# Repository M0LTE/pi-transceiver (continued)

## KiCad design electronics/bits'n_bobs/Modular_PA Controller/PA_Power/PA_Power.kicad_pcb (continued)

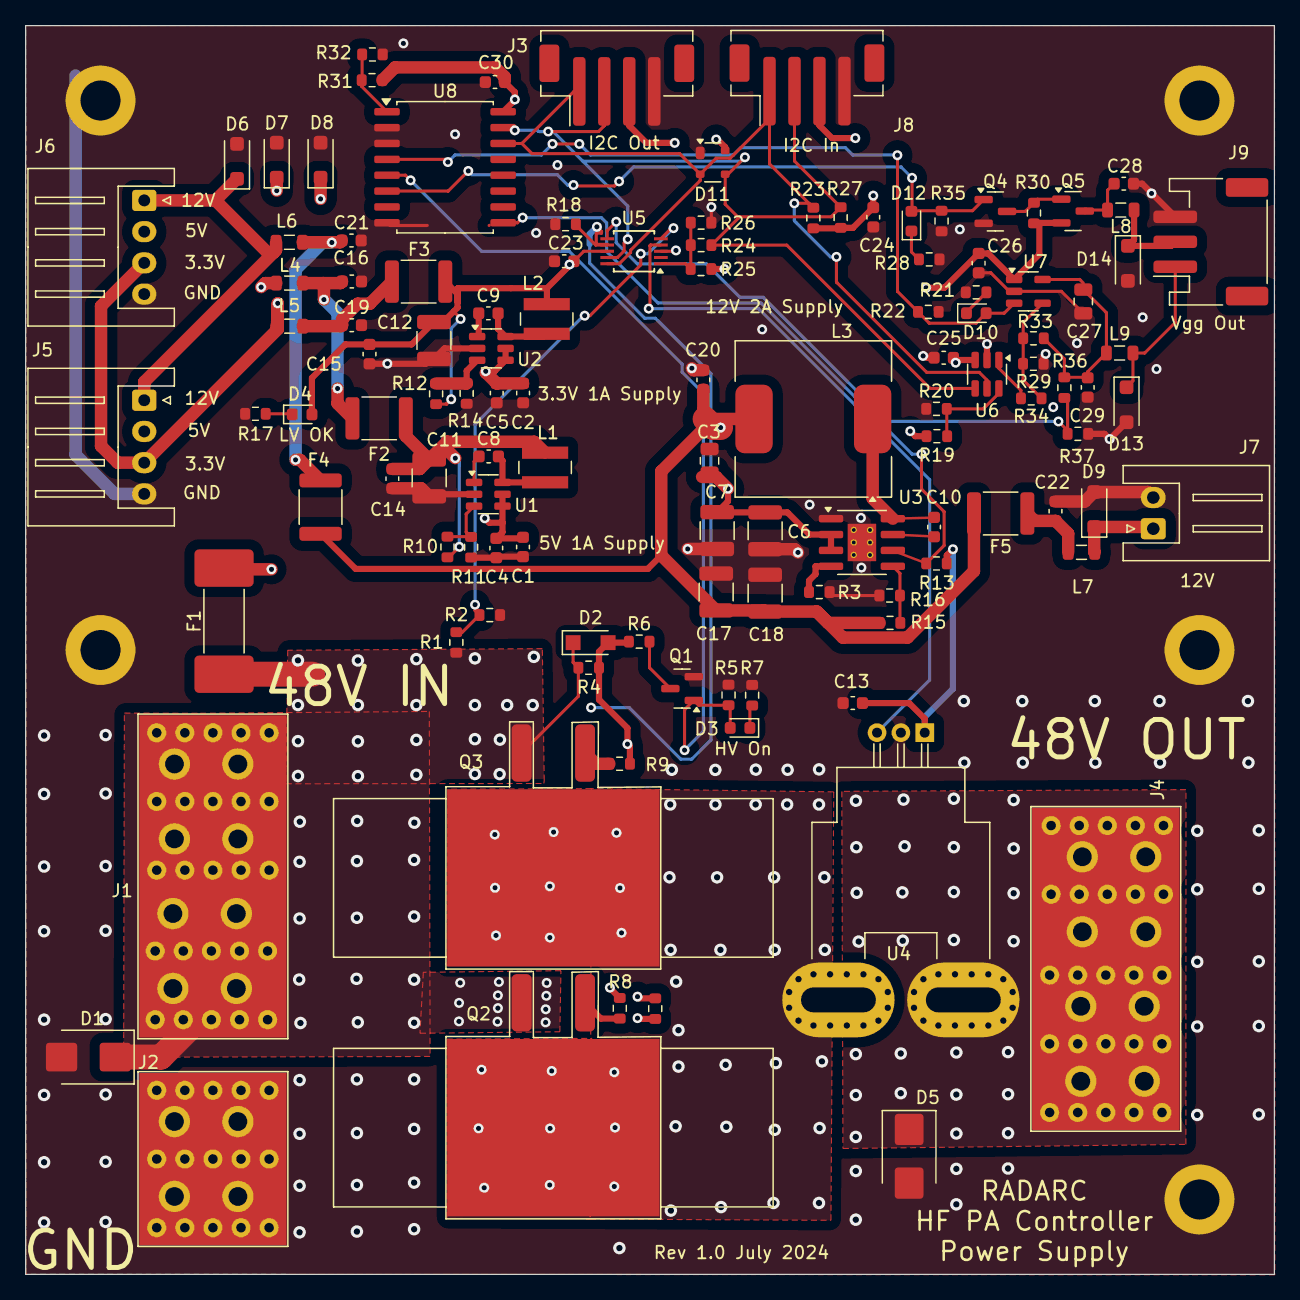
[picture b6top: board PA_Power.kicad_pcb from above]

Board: 4 copper layers, 100.0 x 100.0 mm, 123 parts (0 on the bottom side), 54 nets.

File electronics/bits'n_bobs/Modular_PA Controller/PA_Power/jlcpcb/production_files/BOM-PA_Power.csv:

Comment,Designator,Footprint,LCSC
MountingHole_Pad,H5,MountingHole_3.2mm_M3_DIN965_Pad,
NF,R25,R_0603_1608Metric,
82R,R8,R_0603_1608Metric,
1uH,L9,L_0805_2012Metric,
1A,F4,Fuse_1812_4532Metric,
JST-XH-4,J5,JST_XH_S4B-XH-A_1x04_P2.50mm_Horizontal,
FDN340P,Q5,SOT-23,
JST-XH-4,J6,JST_XH_S4B-XH-A_1x04_P2.50mm_Horizontal,
100n,C25,C_0603_1608Metric,
0R,R32,R_0603_1608Metric,
100n,C22,C_0603_1608Metric,
10k,TH1,R_0603_1608Metric,
1k8,R34,R_0603_1608Metric,
AP2204K-ADJ,U7,SOT-23-5,
1A,F1,Fuse_Schurter_UMZ250,
15uH,L1,L_Wuerth_MAPI-4030,
NF,R24,R_0603_1608Metric,
LMR38020,U3,lmr38012,
PCF8574A,U8,SOIC-16W_7.5x10.3mm_P1.27mm,
4k7,R27,R_0603_1608Metric,
10k,R37,R_0603_1608Metric,
1uH,L8,L_0805_2012Metric,
Green,D4,LED_0603_1608Metric,
64k9,R3,R_0603_1608Metric,
1uH,L6,L_0805_2012Metric,
2.2u,C7,C_1210_3225Metric,
  SQM120P10-19L,Q3,TO263_Heatsink_301,
82R,R9,R_0603_1608Metric,
10k,R7,R_0603_1608Metric,
100n,C16,C_0603_1608Metric,
100n,C20,C_0603_1608Metric,
 JST-XH-2,J7,JST_XH_S2B-XH-A_1x02_P2.50mm_Horizontal,
NF,R31,R_0603_1608Metric,
10k,R30,R_0603_1608Metric,
ADS1015IDGS,U5,TSSOP-10_3x3mm_P0.5mm,
110k,R15,R_0603_1608Metric,
1k,R5,R_0603_1608Metric,
60A 4 Pin,J4,Fat_Power 4,
10k,R36,R_0603_1608Metric,
1uH,L4,L_0805_2012Metric,
100nf,C8,C_0603_1608Metric,
2.2u,C6,C_1210_3225Metric,
10K,R4,R_0603_1608Metric,
1k,R28,R_0603_1608Metric,
100nf,C9,C_0603_1608Metric,
100n,C3,C_0805_2012Metric,
2.2u,C4,C_0603_1608Metric,
100n,C24,C_0603_1608Metric,
100n,C29,C_0603_1608Metric,
22.1k,R14,R_0603_1608Metric,
22u,C11,C_1210_3225Metric,
MountingHole_Pad,H2,MountingHole_3.2mm_M3_DIN965_Pad,
22.1k,R11,R_0603_1608Metric,
100k,R13,R_0603_1608Metric,
4k7,R6,R_0603_1608Metric,
SMF4L5.0A,D13,D_SOD-123F,
60A 4 pin,J1,Fat_Power 4,
0R,R20,R_0603_1608Metric,
270k,R1,R_0603_1608Metric,
33uH,L3,L_Coilcraft_MSS1210-XXX,
100n,C21,C_0603_1608Metric,
NF,R19,R_0603_1608Metric,
10k,R16,R_0603_1608Metric,
1k,R17,R_0603_1608Metric,
1uH,L7,L_0805_2012Metric,
2.2u,C5,C_0603_1608Metric,
LMR50410,U2,SOT-23-6,
1k,R21,R_0603_1608Metric,
ACS770xCB-050B-PFF,U4,Allegro_CB_PFF,
4k7,R23,R_0603_1608Metric,
SMF4L5.0A,D8,D_SOD-123F,
MCP4725A0T,U6,SOT-23-6,
SMF4L12A,D9,D_SOD-123F,
LMR50410,U1,SOT-23-6,
10k,R35,R_0603_1608Metric,
SMF4L5.0A,D7,D_SOD-123F,
SM6T75A,D1,D_SMB,
162k,R10,R_0603_1608Metric,
100n,C14,C_0603_1608Metric,
10k,R18,R_0603_1608Metric,
10k,R2,R_0603_1608Metric,
1A,F2,Fuse_1812_4532Metric,
MountingHole_Pad,H3,MountingHole_3.2mm_M3_DIN965_Pad,
100n,C26,C_0603_1608Metric,
100n,C30,C_0603_1608Metric,
JST-PH-4,J3,JST_PH_B4B-PH-SM4-TB_1x04-1MP_P2.00mm_Vertical,
15uH,L2,L_Wuerth_MAPI-4030,
1k8,R29,R_0603_1608Metric,
100n,C23,C_0603_1608Metric,
4k7,R22,R_0603_1608Metric,
BSS123,Q1,SOT-23,
1A,F5,Fuse_1812_4532Metric,
JST-PH-4,J8,JST_PH_B4B-PH-SM4-TB_1x04-1MP_P2.00mm_Vertical,
100nf,C10,C_0603_1608Metric,
1k,R33,R_0603_1608Metric,
100n,C15,C_0603_1608Metric,
MountingHole_Pad,H4,MountingHole_3.2mm_M3_DIN965_Pad,
0R,R26,R_0603_1608Metric,
100k,R12,R_0603_1608Metric,
30A 2 Pin,J2,Fat_Power 2,
100n,C1,C_0603_1608Metric,
1A,F3,Fuse_1812_4532Metric,
1uH,L5,L_0805_2012Metric,
22u,C17,C_1210_3225Metric,
100n,C2,C_0603_1608Metric,
MountingHole_Pad,H1,MountingHole_3.2mm_M3_DIN965_Pad,
JST-PH-3,J9,JST_PH_S3B-PH-SM4-TB_1x03-1MP_P2.00mm_Horizontal,
  SQM120P10-19L,Q2,TO263_Heatsink_301,
BSS123,Q4,SOT-23,
15v,D2,Nexperia_CFP3_SOD-123W,
SMF4L12A,D14,D_SOD-123F,
Yellow,D12,LED_0603_1608Metric,
SP0503BAHT,D11,SOT-143,
Blue,D10,LED_0603_1608Metric,
SMF4L12A,D6,D_SOD-123F,
SM6T75A,D5,D_SMB,
Red,D3,LED_0603_1608Metric,
100n,C28,C_0603_1608Metric,
22u,C27,C_0805_2012Metric,
22u,C18,C_1210_3225Metric,
100n,C19,C_0603_1608Metric,
22u,C12,C_1210_3225Metric,
100n,C13,C_0603_1608Metric,

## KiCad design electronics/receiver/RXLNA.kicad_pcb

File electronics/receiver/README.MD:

This is the proposed design for the Receiver PCB including Low Noise Amplifier, Band Pass Filter and RF path switching.
The band pass filter is 4 pole butterworth with 1dB bandwidth of 144.0 to 147.0 MHz.  It is switched between receive and transmit paths. 
The low noise amplifier has a 2dB noise figure.  It has protection against antenna relay leakage and close-by transmitters.  It has a gain of 25dB.  Provision is made to attenuate the Receiver gain by a fixed amount of 20dB to optimse strong signal performance.
RFswitching is provided for Receive/Transmit switching.  A monitor channel is provided to allow the LimeSDR Mini receiver to monitor the attenuated transmit signal.
The switching is capable of allowing use of a half duplex SDR in place of the LimeSDR Mini.
The inductors in the 4 pole bandpas filter are screened using 22mm pipe caps (copper).  With care and sutable shielding using kapton tape or PTFE thermal insulation it should be possible to solder these after the board has been fitted with all smd devices and tested.  I am not sure but it may be necessary to fit the trimmer capacitors last.  Work is still ongoing to determine the requirements for soldering the pipe caps.

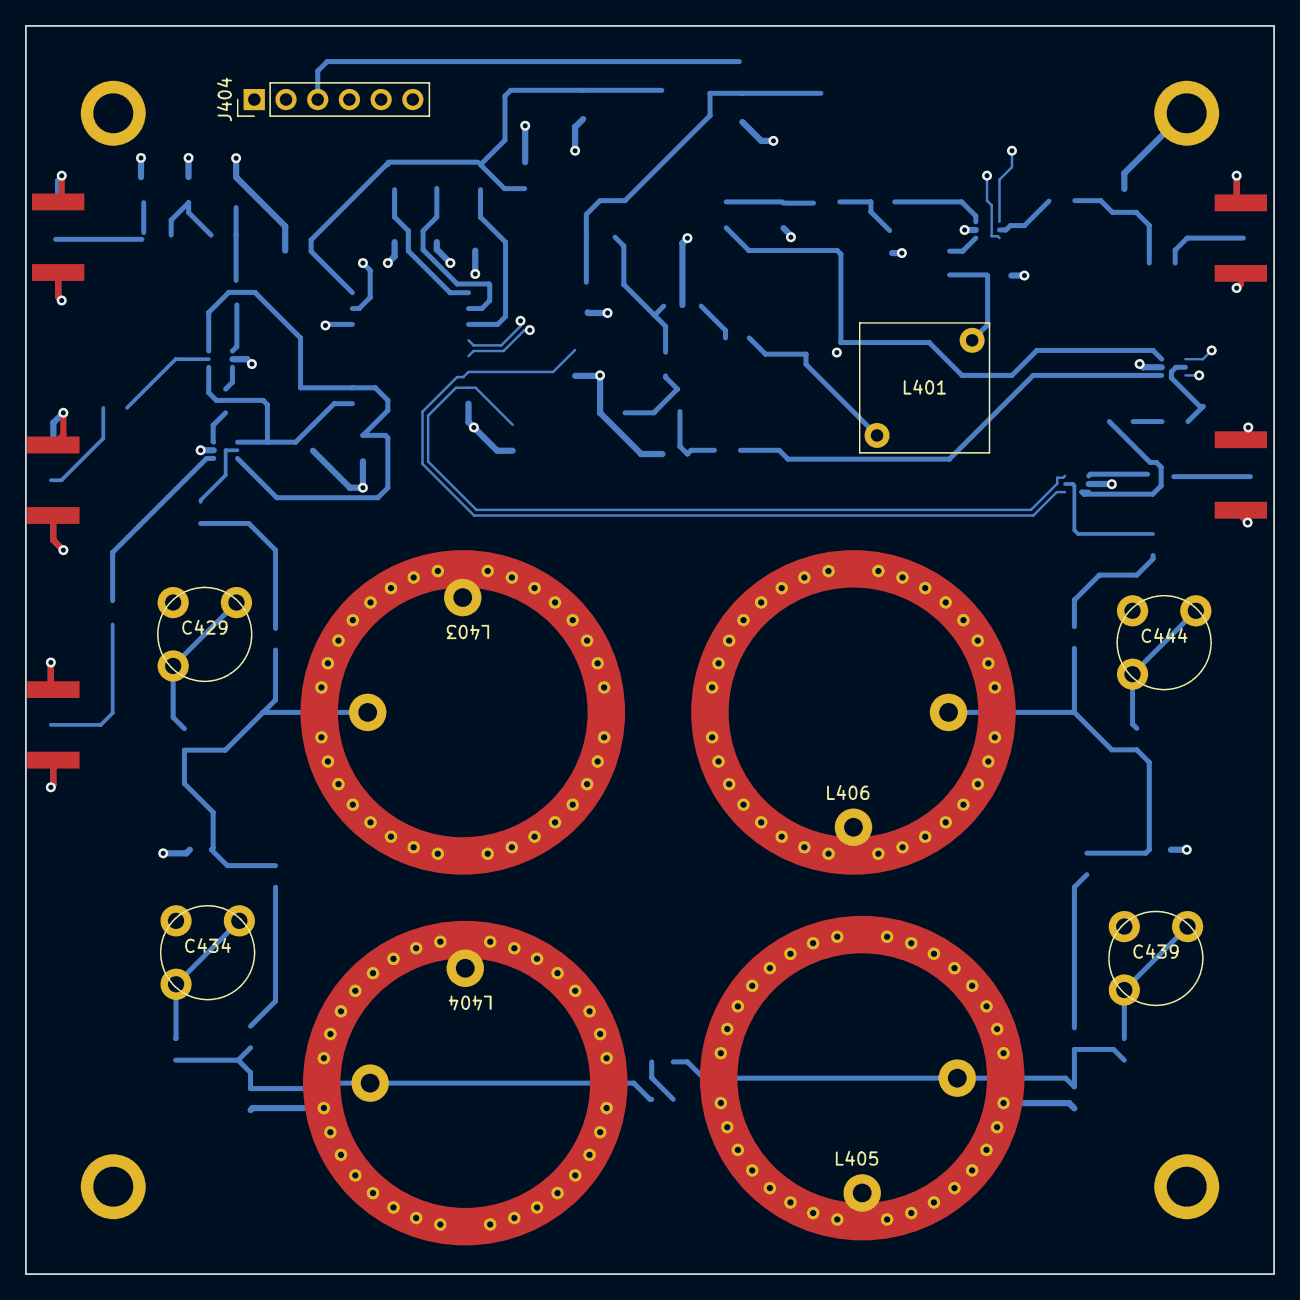
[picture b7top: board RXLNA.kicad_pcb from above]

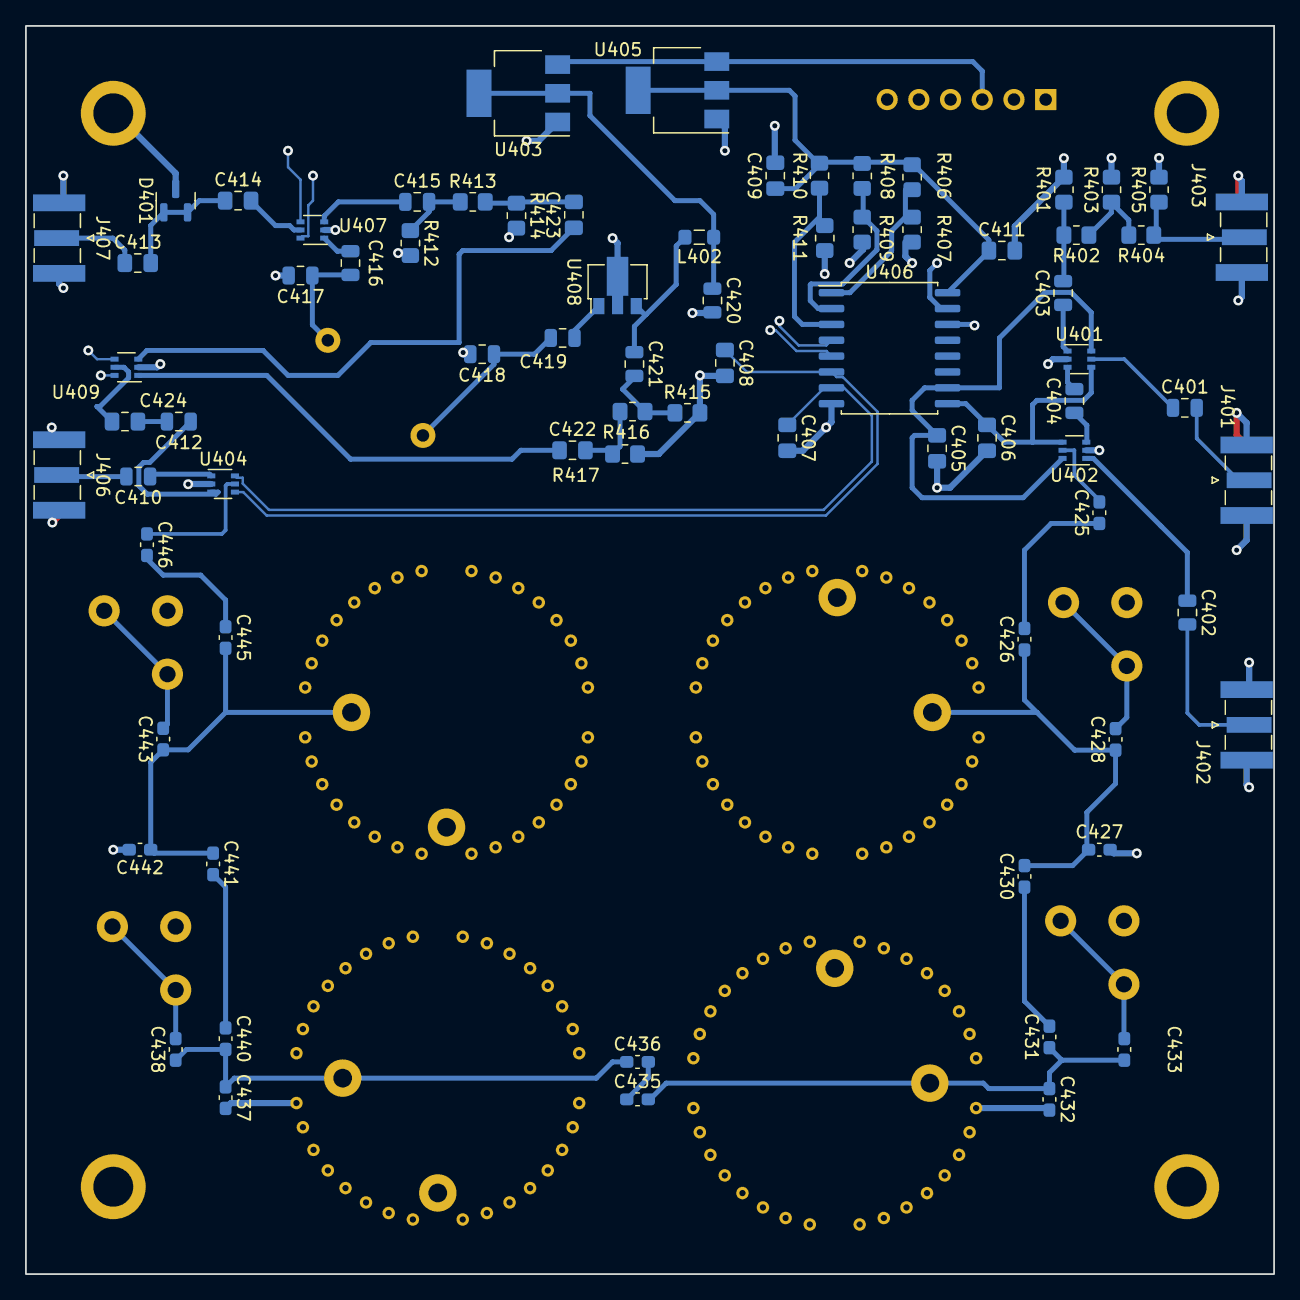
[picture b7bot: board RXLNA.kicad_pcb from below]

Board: 4 copper layers, 100.0 x 100.0 mm, 86 parts (75 on the bottom side), 60 nets.

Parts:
C401, C402, C403, C404, C410, C412, C415, C416, C419, C421: 1n0; C_0805_2012Metric
C405, C406, C407, C408: 100p; C_0805_2012Metric_Pad1.18x1.45mm_HandSolder
C409, C411: 100n; C_0805_2012Metric_Pad1.18x1.45mm_HandSolder
C413, C414, C422, C423, C424: 1n0; C_0805_2012Metric_Pad1.18x1.45mm_HandSolder
C417, C418: C; C_0805_2012Metric
C420: 100n; C_0805_2012Metric
C425: 15p; C_0603_1608Metric_Pad1.08x0.95mm_HandSolder
C426, C430, C445: 6p8; C_0603_1608Metric_Pad1.08x0.95mm_HandSolder
C427: 8p2; C_0603_1608Metric_Pad1.08x0.95mm_HandSolder
C428: 18p; C_0603_1608Metric_Pad1.08x0.95mm_HandSolder
C429, C434, C439, C444: 5-22pF; TrimCap
C431: 0p7; C_0603_1608Metric_Pad1.08x0.95mm_HandSolder
C432, C437, C442: 12p0; C_0603_1608Metric_Pad1.08x0.95mm_HandSolder
C433, C438: 22p0; C_0603_1608Metric_Pad1.08x0.95mm_HandSolder
C435: 0p9; C_0603_1608Metric_Pad1.08x0.95mm_HandSolder
C436, C441: 0p5; C_0603_1608Metric_Pad1.08x0.95mm_HandSolder
C440: 1p8; C_0603_1608Metric_Pad1.08x0.95mm_HandSolder
C443: 15p0; C_0603_1608Metric_Pad1.08x0.95mm_HandSolder
C446: 3p9; C_0603_1608Metric_Pad1.08x0.95mm_HandSolder
D401: SMP1330-005LF; SOT-23
J401, J402, J403, J406, J407: Conn_Coaxial; SMA_Samtec_SMA-J-P-X-ST-EM1_EdgeMount
J404: Conn_01x06_Male; PinHeader_1x06_P2.54mm_Vertical
J405: Conn_01x01_Male; Board outline 100_100
L401: L_Trim; L_Radial_L10.2mm_W10.2mm_Px7.62mm_Py7.62mm_Pulse_LP-30
L402: L; L_0805_2012Metric_Pad1.05x1.20mm_HandSolder
L403, L404, L405, L406: 54n6; Pipe22
R401, R402, R403, R404, R405, R406, R407, R408, R409, R410, R411, R412, R413, R414, R415, R416, R417: R; R_0805_2012Metric_Pad1.20x1.40mm_HandSolder
U401, U402, U404, U407, U409: AS179-92LF; SOT-363_SC-70-6
U403: AMS1117-5.0; SOT-223-3_TabPin2
U405: AMS1117-3.3; SOT-223-3_TabPin2
U406: PCF8574A; SOIC-16W_7.5x10.3mm_P1.27mm
U408: PSA4-5043; SOT-89-3

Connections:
+3.3V: C409.1, C411.1, R406.1, R408.1, R410.1, U405.2 (VO), U406.16 (VDD)
+5V: C420.1, L402.1, U403.2 (VO)
+12V: J404.3, U403.3 (VI), U405.3 (VI)
/LNA/+25dBm max: C416.2, U407.1 (J3)
/LNA/PIN Limiter: C413.2, C414.1, D401.1 (K), D401.2 (K)
/PIN Switch/LimeRx: C401.2, J401.1 (In)
/PIN Switch/LimeTx: C402.2, J402.1 (In)
/PIN Switch/Rx_Enable: C405.1, U401.6 (V2), U402.6 (V2), U406.10 (P5)
/PIN Switch/SCL_Slave: J404.5, U406.14 (SCL)
/PIN Switch/SDA_Slave: J404.6, U406.15 (SDA)
/PIN Switch/Tx_Drive: C410.2, J406.1 (In)
/PIN Switch/Tx_Enable: C406.1, U401.4 (V1), U402.4 (V1), U406.9 (P4)
/PIN Switch/Tx_N: C407.1, U404.6 (V2), U406.7 (P3)
/PIN Switch/Tx_P: C408.1, U404.4 (V1), U406.6 (P2)
BPF_In: C425.2, U402.5 (J1)
BPF_Out: C446.1, U404.5 (J1)
GND: C405.2, C406.2, C407.2, C408.2, C409.2, C411.2, C417.2, C418.2, C420.2, C427.2, C429.2, C432.2, C434.2, C437.2, C439.2, C442.2, C444.2, D401.3 (A), J401.2 (Ext), J402.2 (Ext), J403.2 (Ext), J404.1, J404.2, J404.4, J405.1, J406.2 (Ext), J407.2 (Ext), L403.2, L404.2, L405.2, L406.2, R401.2, R403.2, R405.2, R407.2, R409.2, R411.2, R412.2, R414.2, R415.2, R417.2, U401.2 (GND), U402.2 (GND), U403.1 (GND), U404.2 (GND), U405.1 (GND), U406.8 (VSS), U407.2 (GND), U408.2 (GND), U409.2 (GND)
LNA_N: U406.4 (P0), U407.4 (V1), U409.4 (V1)
LNA_P: U406.5 (P1), U407.6 (V2), U409.6 (V2)
unnamed: C403.2, R401.1, R402.2
unnamed: C415.2, R412.1, R413.1
unnamed: C416.1, C417.1, L401.1
unnamed: C418.1, C419.2, L401.2
unnamed: C419.1, U408.1
unnamed: C421.1, L402.2, U408.3
unnamed: C421.2, R415.1, R416.1
unnamed: C422.2, R416.2, R417.1
unnamed: C423.2, R413.2, R414.1
unnamed: C425.1, C426.2
unnamed: C426.1, C427.1, C428.1, C430.2, L403.1
unnamed: C428.2, C429.1
unnamed: C430.1, C431.2
unnamed: C431.1, C432.1, C433.1, C435.2, L404.1
unnamed: C433.2, C434.1
unnamed: C435.1, C436.2
unnamed: C436.1, C437.1, C438.1, C440.2, L405.1
unnamed: C438.2, C439.1
unnamed: C440.1, C441.2
unnamed: C441.1, C442.1, C443.1, C445.2, L406.1
unnamed: C443.2, C444.1
unnamed: C445.1, C446.2
unnamed: J403.1 (In), R404.1, R405.1
unnamed: R402.1, R403.1, R404.2
unnamed: C401.1, U401.5 (J1)
unnamed: C404.2, U401.3 (J2)
unnamed: C403.1, U401.1 (J3)
unnamed: C404.1, U402.3 (J2)
unnamed: C402.1, U402.1 (J3)
unnamed: C412.1, U404.3 (J2)
unnamed: C410.1, U404.1 (J3)
unnamed: R406.2, R407.1, U406.1 (A0)
unnamed: R408.2, R409.1, U406.2 (A1)
unnamed: R410.2, R411.1, U406.3 (A2)
unnamed: C414.2, U407.5 (J1)
unnamed: C415.1, U407.3 (J2)
unnamed: C424.1, U409.5 (J1)
unnamed: C423.1, U409.3 (J2)
unnamed: C422.1, U409.1 (J3)
RxIP: C413.1, J407.1 (In)
Rx_LNA_OP: C412.2, C424.2

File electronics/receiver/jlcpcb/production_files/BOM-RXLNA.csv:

Comment,Designator,Footprint,LCSC
100n,"C409,C411,C420",C_0805_2012Metric_Pad1.18x1.45mm_HandSolder,C111492
SMP1330-005LF,D401,SOT-23,C150870
AMS1117-3.3,U405,SOT-223-3_TabPin2,C5199435
PSA4-5043,U408,SOT-89-3,C5240848
100p,"C405,C406,C407,C408",C_0805_2012Metric_Pad1.18x1.45mm_HandSolder,C62768
1n0,"C401,C402,C403,C404,C410,C412,C413,C414,C415,C416,C419,C421,C422,C423,C424",C_0805_2012Metric,C62774
AS179-92LF,"U401,U402,U404,U407,U409",SOT-363_SC-70-6,C83422
PCF8574A,U406,SOIC-16W_7.5x10.3mm_P1.27mm,C86832
AMS1117-5.0,U403,SOT-223-3_TabPin2,C917153
L_Trim,L401,L_Radial_L10.2mm_W10.2mm_Px7.62mm_Py7.62mm_Pulse_LP-30,
54n6,L403,Pipe22,
5-22pF,C439,TrimCap,
5-22pF,C429,TrimCap,
54n6,L406,Pipe22,
5-22pF,C444,TrimCap,
Conn_01x06_Male,J404,PinHeader_1x06_P2.54mm_Vertical,
54n6,L405,Pipe22,
54n6,L404,Pipe22,
5-22pF,C434,TrimCap,
Conn_01x01_Male,J405,Board outline 100_100,
R,R406,R_0805_2012Metric_Pad1.20x1.40mm_HandSolder,
R,R408,R_0805_2012Metric_Pad1.20x1.40mm_HandSolder,
12p0,C442,C_0603_1608Metric_Pad1.08x0.95mm_HandSolder,
R,R403,R_0805_2012Metric_Pad1.20x1.40mm_HandSolder,
R,R411,R_0805_2012Metric_Pad1.20x1.40mm_HandSolder,
R,R414,R_0805_2012Metric_Pad1.20x1.40mm_HandSolder,
Conn_Coaxial,J407,SMA_Samtec_SMA-J-P-X-ST-EM1_EdgeMount,
0p9,C435,C_0603_1608Metric_Pad1.08x0.95mm_HandSolder,
Conn_Coaxial,J401,SMA_Samtec_SMA-J-P-X-ST-EM1_EdgeMount,
R,R409,R_0805_2012Metric_Pad1.20x1.40mm_HandSolder,
8p2,C427,C_0603_1608Metric_Pad1.08x0.95mm_HandSolder,
Conn_Coaxial,J403,SMA_Samtec_SMA-J-P-X-ST-EM1_EdgeMount,
C,C418,C_0805_2012Metric,
R,R416,R_0805_2012Metric_Pad1.20x1.40mm_HandSolder,
R,R401,R_0805_2012Metric_Pad1.20x1.40mm_HandSolder,
22p0,C438,C_0603_1608Metric_Pad1.08x0.95mm_HandSolder,
R,R405,R_0805_2012Metric_Pad1.20x1.40mm_HandSolder,
R,R415,R_0805_2012Metric_Pad1.20x1.40mm_HandSolder,
R,R417,R_0805_2012Metric_Pad1.20x1.40mm_HandSolder,
Conn_Coaxial,J406,SMA_Samtec_SMA-J-P-X-ST-EM1_EdgeMount,
0p7,C431,C_0603_1608Metric_Pad1.08x0.95mm_HandSolder,
R,R402,R_0805_2012Metric_Pad1.20x1.40mm_HandSolder,
L,L402,L_0805_2012Metric_Pad1.05x1.20mm_HandSolder,
R,R410,R_0805_2012Metric_Pad1.20x1.40mm_HandSolder,
3p9,C446,C_0603_1608Metric_Pad1.08x0.95mm_HandSolder,
15p,C425,C_0603_1608Metric_Pad1.08x0.95mm_HandSolder,
15p0,C443,C_0603_1608Metric_Pad1.08x0.95mm_HandSolder,
Conn_Coaxial,J402,SMA_Samtec_SMA-J-P-X-ST-EM1_EdgeMount,
R,R413,R_0805_2012Metric_Pad1.20x1.40mm_HandSolder,
6p8,C445,C_0603_1608Metric_Pad1.08x0.95mm_HandSolder,
0p5,C441,C_0603_1608Metric_Pad1.08x0.95mm_HandSolder,
R,R404,R_0805_2012Metric_Pad1.20x1.40mm_HandSolder,
6p8,C430,C_0603_1608Metric_Pad1.08x0.95mm_HandSolder,
R,R412,R_0805_2012Metric_Pad1.20x1.40mm_HandSolder,
22p0,C433,C_0603_1608Metric_Pad1.08x0.95mm_HandSolder,
12p0,C432,C_0603_1608Metric_Pad1.08x0.95mm_HandSolder,
6p8,C426,C_0603_1608Metric_Pad1.08x0.95mm_HandSolder,
C,C417,C_0805_2012Metric,
18p,C428,C_0603_1608Metric_Pad1.08x0.95mm_HandSolder,
0p5,C436,C_0603_1608Metric_Pad1.08x0.95mm_HandSolder,
R,R407,R_0805_2012Metric_Pad1.20x1.40mm_HandSolder,
1p8,C440,C_0603_1608Metric_Pad1.08x0.95mm_HandSolder,
12p0,C437,C_0603_1608Metric_Pad1.08x0.95mm_HandSolder,

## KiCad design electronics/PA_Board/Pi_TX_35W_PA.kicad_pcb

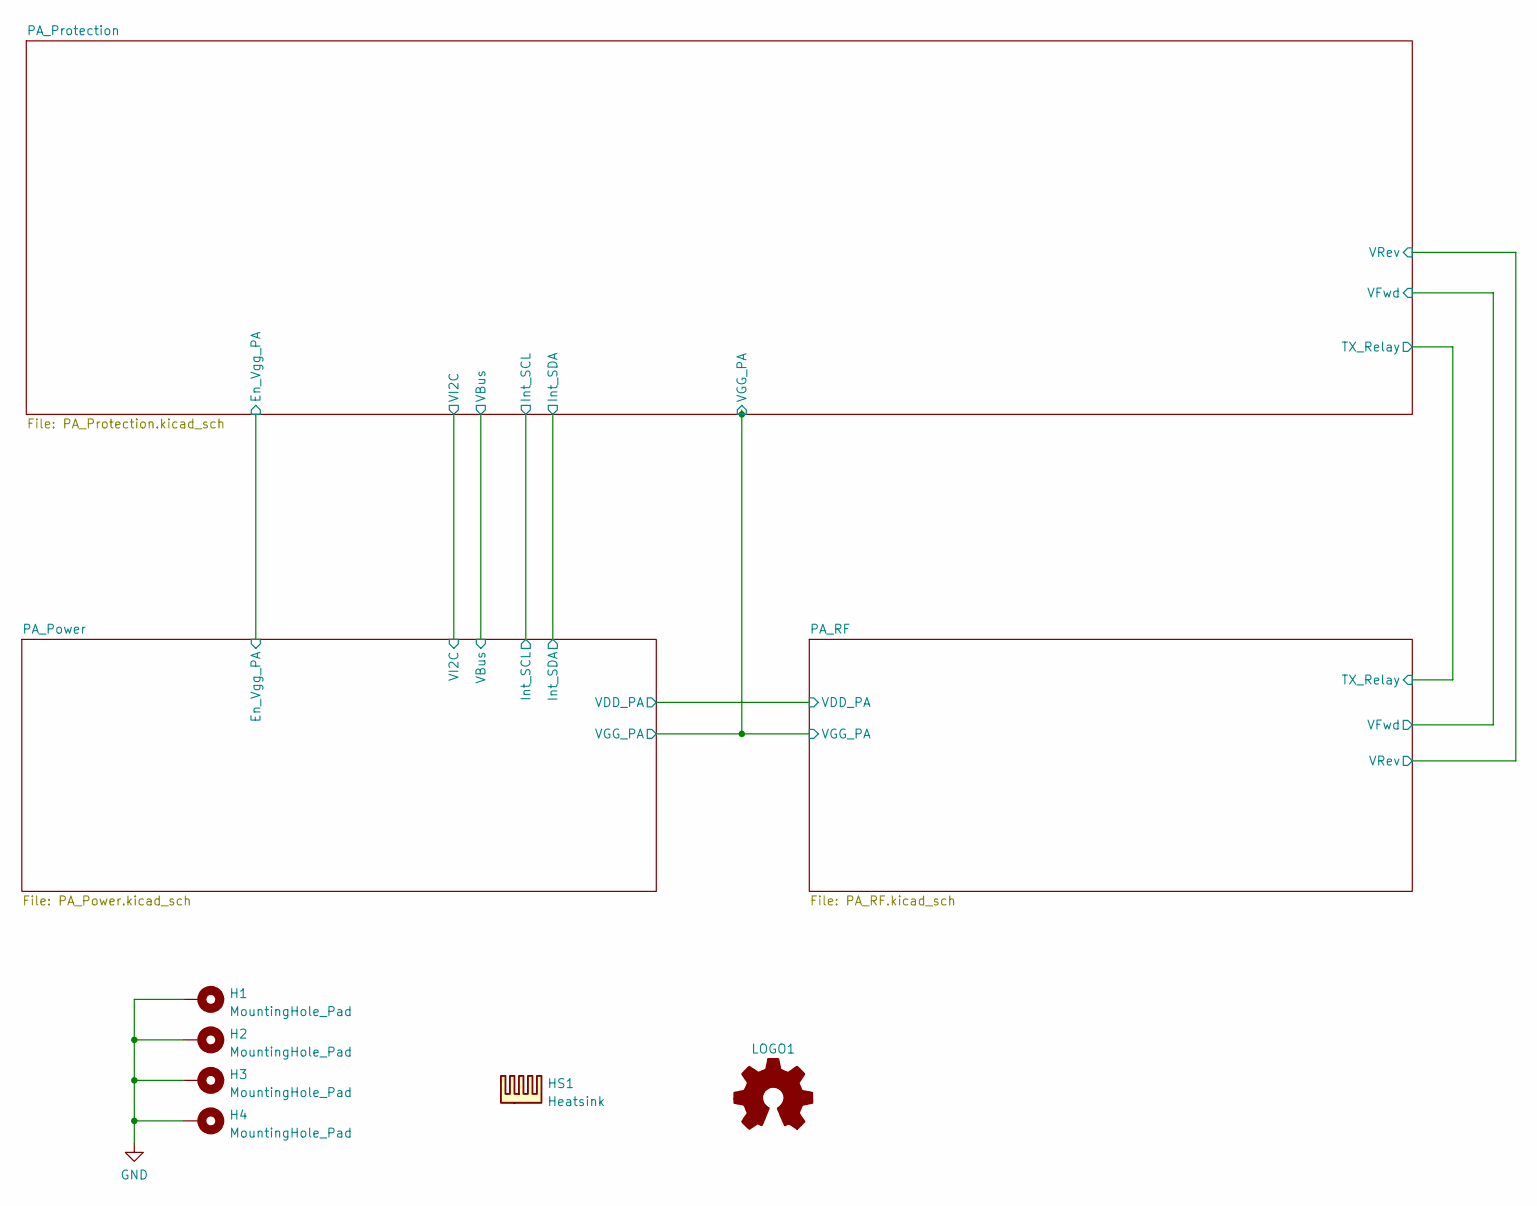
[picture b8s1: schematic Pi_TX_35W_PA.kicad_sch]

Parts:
H1, H2, H3, H4: MountingHole_Pad; MountingHole_4.3mm_M4_DIN965_Pad
HS1: Heatsink; Copper_Pad
LOGO1: Logo_Open_Hardware_Small; OSHW-Logo2_9.8x8mm_SilkScreen

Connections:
GND: H1.1, H2.1, H3.1, H4.1; also elsewhere on the board

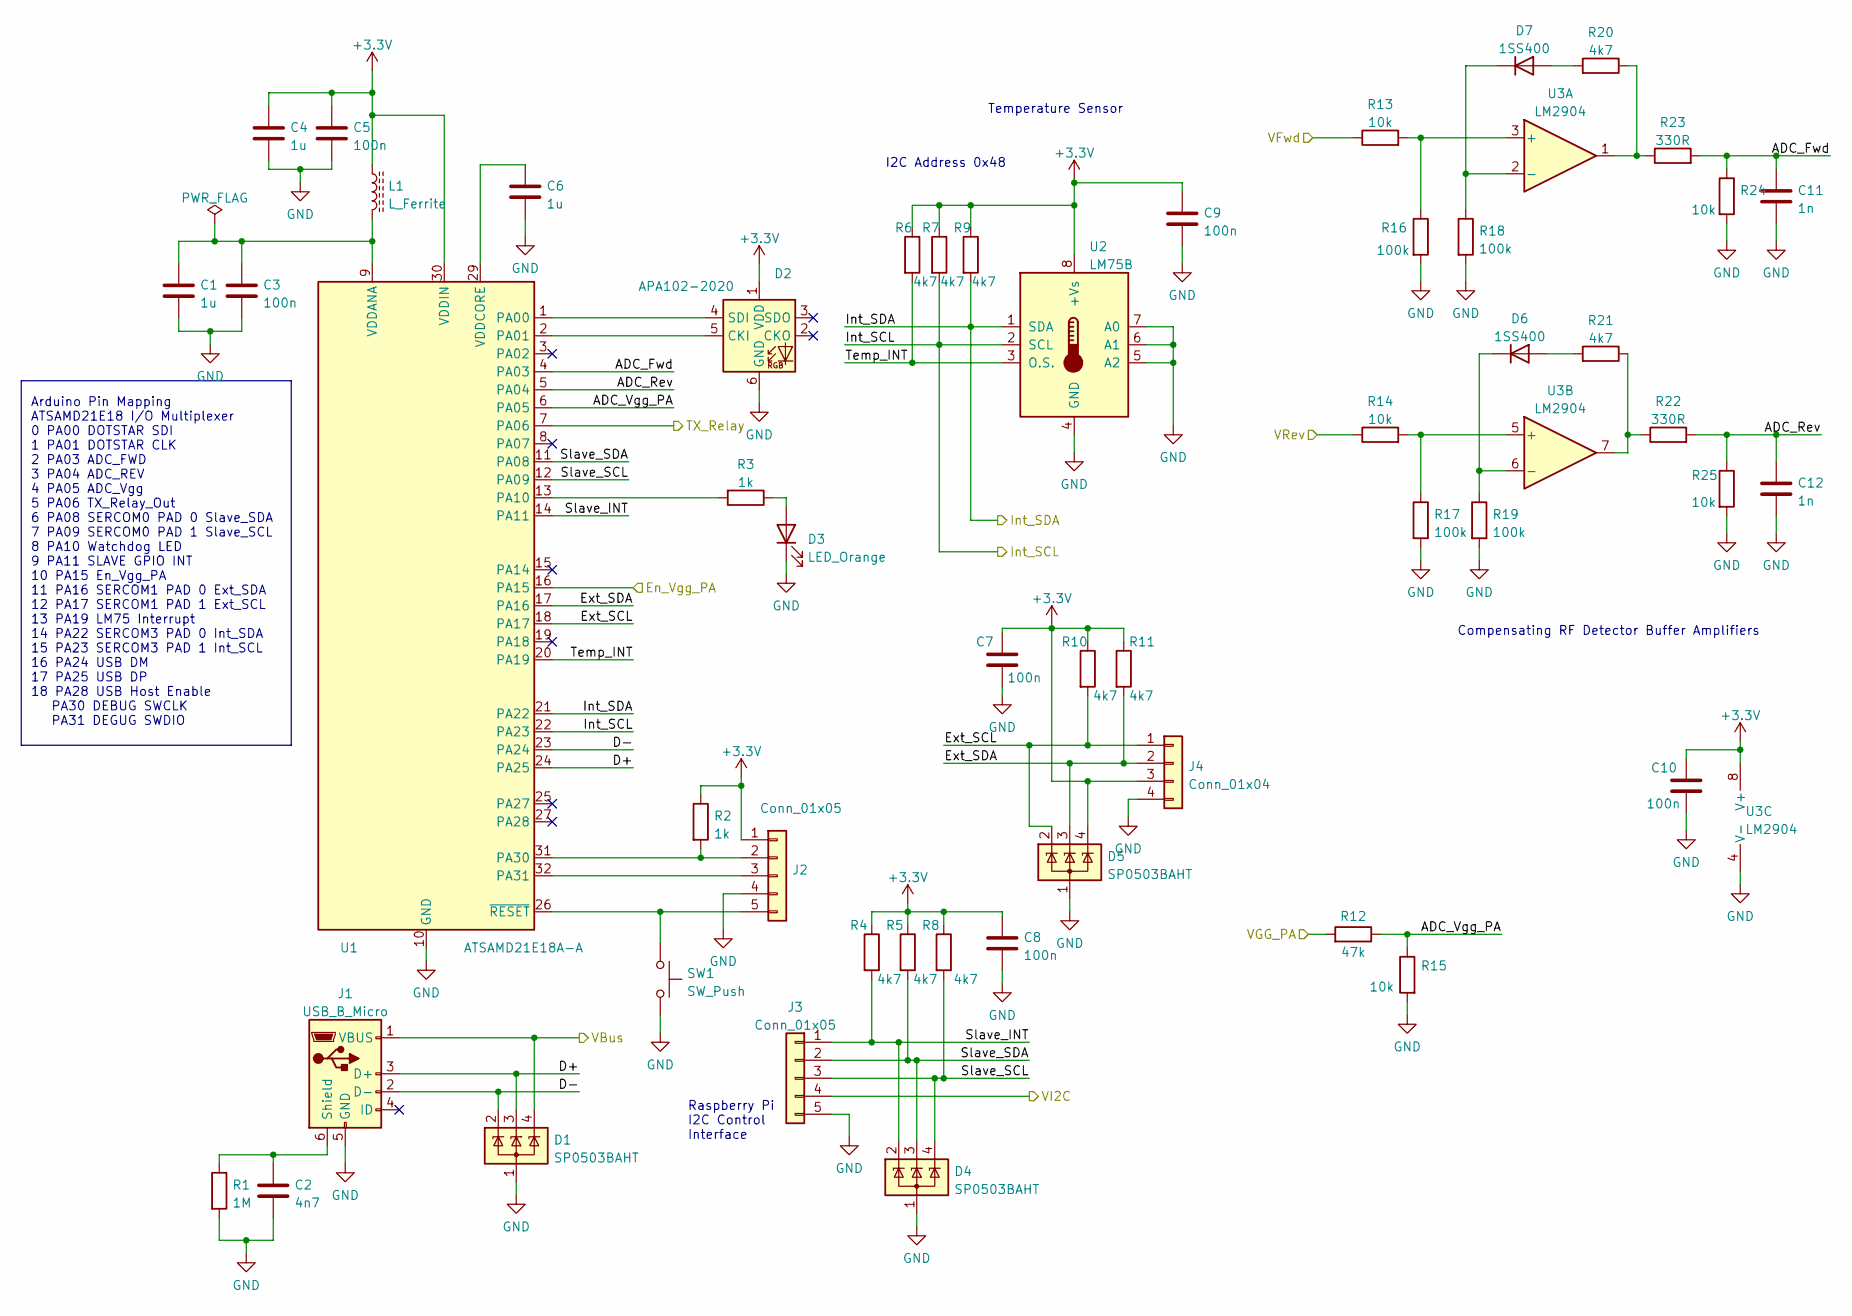
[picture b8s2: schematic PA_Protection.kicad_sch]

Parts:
C1, C4, C6: 1u; C_0603_1608Metric
C2: 4n7; C_0603_1608Metric
C3, C5, C7, C8, C9, C10: 100n; C_0603_1608Metric
C11, C12: 1n; C_0603_1608Metric
D1, D4, D5: SP0503BAHT; SOT-143
D2: APA102-2020; LED-APA102-2020
D3: LED_Orange; LED_0603_1608Metric
D6, D7: 1SS400; D_SOD-523
J1: USB_B_Micro; USB_Micro-B_Molex-105017-0001
J2: Conn_01x05; Debug_Clip
J3: Conn_01x05; JST_PH_S5B-PH-SM4-TB_1x05-1MP_P2.00mm_Horizontal
J4: Conn_01x04; JST_PH_S4B-PH-SM4-TB_1x04-1MP_P2.00mm_Horizontal
L1: L_Ferrite; L_0603_1608Metric
R1: 1M; R_0603_1608Metric
R2, R3: 1k; R_0603_1608Metric
R4, R5, R6, R7, R8, R9, R10, R11, R20, R21: 4k7; R_0603_1608Metric
R12: 47k; R_0603_1608Metric
R13, R14, R15, R24, R25: 10k; R_0603_1608Metric
R16, R17, R18, R19: 100k; R_0603_1608Metric
R22, R23: 330R; R_0603_1608Metric
SW1: SW_Push; Panasonic_EVQPUL_EVQPUC
U1: ATSAMD21E18A-A; TQFP-32_7x7mm_P0.8mm
U2: LM75B; SOIC-8_3.9x4.9mm_P1.27mm
U3: LM2904; SOIC-8_3.9x4.9mm_P1.27mm

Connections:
+3.3V: C4.1, C5.1, C7.1, C8.1, C9.1, C10.1, D2.1 (VDD), D5.4 (K), J2.1, J4.3, L1.1, R2.1, R4.1, R5.1, R6.1, R7.1, R8.1, R9.1, R10.1, R11.1, U1.30 (VDDIN), U2.8 (+Vs), U3.8 (V+); also elsewhere on the board
/PA_Power/En_Vgg_PA: U1.16 (PA15); also elsewhere on the board
/PA_Power/Int_SCL: R7.2, U1.22 (PA23), U2.2 (SCL); also elsewhere on the board
/PA_Power/Int_SDA: R9.2, U1.21 (PA22), U2.1 (SDA); also elsewhere on the board
/PA_Power/VBus: D1.4 (K), J1.1 (VBUS); also elsewhere on the board
/PA_Power/VGG_PA: R12.2; also elsewhere on the board
/PA_Power/VI2C: J3.4; also elsewhere on the board
/PA_Protection/ADC_Fwd: C11.1, R23.2, R24.1, U1.4 (PA03)
/PA_Protection/ADC_Rev: C12.1, R22.2, R25.1, U1.5 (PA04)
/PA_Protection/ADC_Vgg_PA: R12.1, R15.1, U1.6 (PA05)
/PA_Protection/D+: D1.3 (K), J1.3 (D+), U1.24 (PA25)
/PA_Protection/D-: D1.2 (K), J1.2 (D-), U1.23 (PA24)
/PA_Protection/Ext_SCL: D5.2 (K), J4.1, R10.2, U1.18 (PA17)
/PA_Protection/Ext_SDA: D5.3 (K), J4.2, R11.2, U1.17 (PA16)
/PA_Protection/Slave_INT: D4.2 (K), J3.1, R4.2, U1.14 (PA11)
/PA_Protection/Slave_SCL: D4.4 (K), J3.3, R8.2, U1.12 (PA09)
/PA_Protection/Slave_SDA: D4.3 (K), J3.2, R5.2, U1.11 (PA08)
/PA_Protection/TX_Relay: U1.7 (PA06); also elsewhere on the board
/PA_Protection/Temp_INT: R6.2, U1.20 (PA19), U2.3 (O.S.)
/PA_Protection/VFwd: R13.1; also elsewhere on the board
/PA_Protection/VRev: R14.1; also elsewhere on the board
GND: C1.2, C2.2, C3.2, C4.2, C5.2, C6.2, C7.2, C8.2, C9.2, C10.2, C11.2, C12.2, D1.1 (A), D2.6 (GND), D3.1 (K), D4.1 (A), D5.1 (A), J1.5 (GND), J2.4, J3.5, J4.4, R1.2, R15.2, R16.2, R17.2, R18.2, R19.2, R24.2, R25.2, SW1.2, U1.10 (GND), U1.28 (GND), U2.4 (GND), U2.5 (A2), U2.6 (A1), U2.7 (A0), U3.4 (V-); also elsewhere on the board
unnamed: C1.1, C3.1, L1.2, U1.9 (VDDANA)
unnamed: C2.1, J1.6 (Shield), R1.1
unnamed: C6.1, U1.29 (VDDCORE)
unnamed: D2.4 (SDI), U1.1 (PA00)
unnamed: D2.5 (CKI), U1.2 (PA01)
unnamed: D3.2 (A), R3.1
unnamed: D6.1 (K), R19.1, U3.6 (-)
unnamed: D6.2 (A), R21.2
unnamed: D7.1 (K), R18.1, U3.2 (-)
unnamed: D7.2 (A), R20.2
unnamed: J2.2, R2.2, U1.31 (PA30)
unnamed: J2.3, U1.32 (PA31)
unnamed: J2.5, SW1.1, U1.26 (~RESET)
unnamed: R3.2, U1.13 (PA10)
unnamed: R13.2, R16.1, U3.3 (+)
unnamed: R14.2, R17.1, U3.5 (+)
unnamed: R20.1, R23.1, U3.1
unnamed: R21.1, R22.1, U3.7

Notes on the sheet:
I2C Address 0x48
Arduino Pin Mapping ATSAMD21E18 I/O Multiplexer 0 PA00 DOTSTAR SDI 1 PA01 DOTSTAR CLK 2 PA03 ADC_FWD 3 PA04 ADC_REV 4 PA05 ADC_Vgg 5 PA06 TX_Relay_Out 6 PA08 SERCOM0 PAD 0 Slave_SDA 7 PA09 SERCOM0 PAD 1 Slave_SCL 8 PA10 Watchdog LED 9 PA11 SLAVE GPIO INT 10 PA15 En_Vgg_PA 11 PA16 SERCOM1 PAD 0 Ext_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
Temperature Sensor
Raspberry Pi I2C Control Interface
Compensating RF Detector Buffer Amplifiers
